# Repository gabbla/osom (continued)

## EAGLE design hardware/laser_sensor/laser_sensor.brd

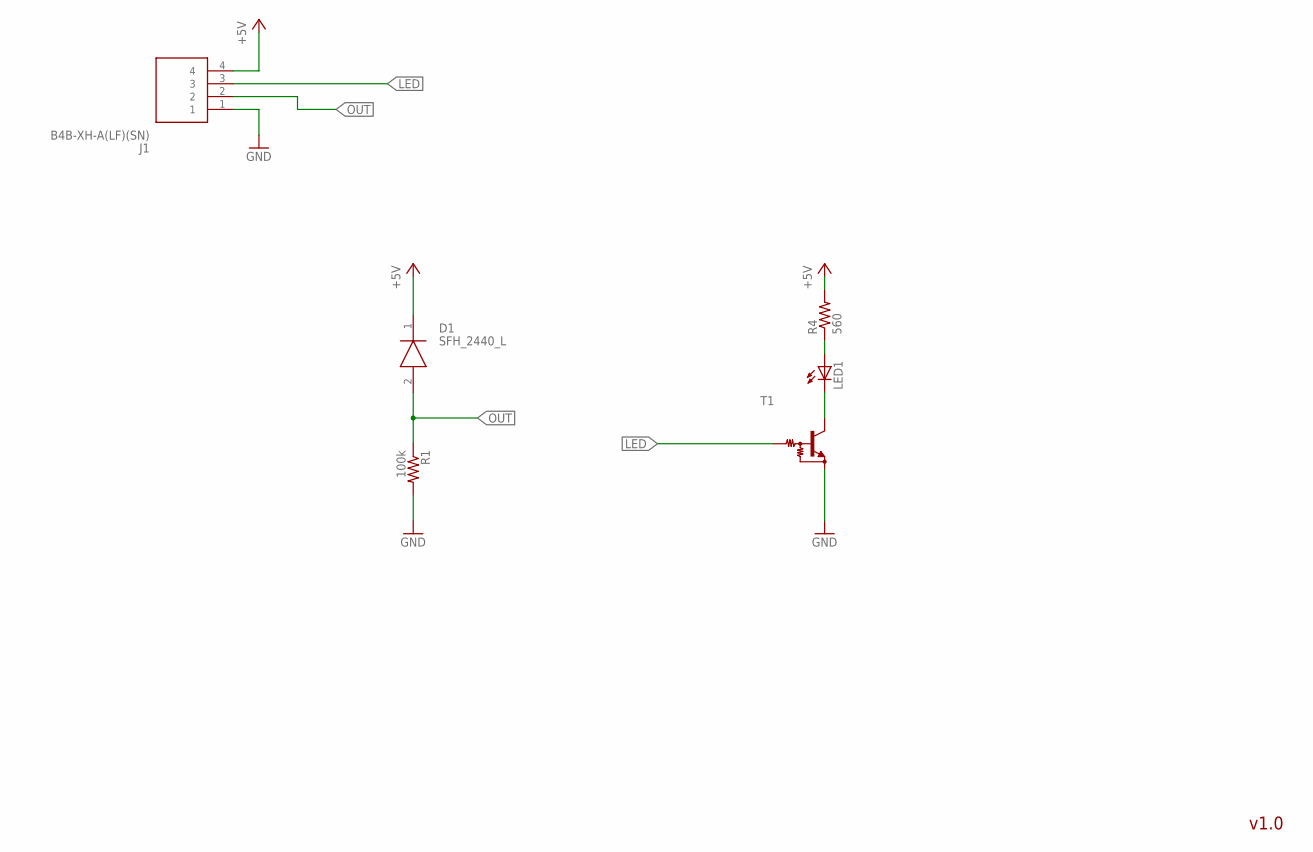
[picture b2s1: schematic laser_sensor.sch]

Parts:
D1: SFH_2440_L; SFH2440L
J1: B4B-XH-A(LF)(SN); SHDR4W64P0X250_1X4_1240X575X70
LED1: LED3MM
R1: 100k; R0603
R4: 560; R0603
T1: MUN2214T1-NPN_DRIVER-SC59-BEC; SC59-BEC

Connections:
+5V: D1.1 (ANODE), J1.4, R4.2
GND: J1.1, R1.2, T1.E
LED: J1.3, T1.B
unnamed: LED1.A, R4.1
unnamed: LED1.K (C), T1.C
OUT: D1.2 (CATHODE), J1.2, R1.1

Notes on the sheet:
v1.0

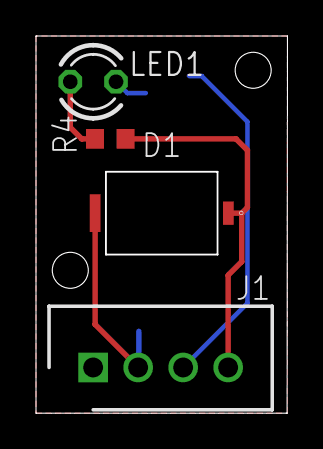
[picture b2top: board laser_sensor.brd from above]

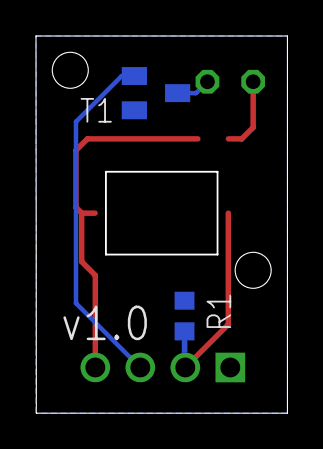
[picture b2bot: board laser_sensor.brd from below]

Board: 2 copper layers, 13.9 x 20.9 mm, 6 parts (2 on the bottom side), 6 nets.

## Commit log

2018-04-15 README.md edited online with Bitbucket
2018-07-07 First draft about CC2541
2018-07-07 First hardwere draft
2018-07-15 - Eagle libraries added - Initial import
2018-07-18 Pin functions and number updated
2018-07-18 IAR test workspace initial commit
2018-07-19 Added CC2541 links
2018-07-29 First IAR workspace draft THAT COMPILES and LINK A no-limit license is needed
2018-08-08 First draft about new arch
2018-08-09 Added debug uart Minor changes
2018-08-09 IAR test deletion
2018-08-09 Gitignore added
2018-08-09 IAR stuff.. to lazy to track them. I won't use them anymore
2018-08-09 PIC32 datasheet added
2018-08-09 Various Eagle library added
2018-08-10 Added regexp to exclude Eagle cad temp files
2018-08-10 Update hw analysis
2018-08-10 Tables fix
2018-08-10 Typo
2018-08-10 Ignore pdf
2018-08-10 .gitignore cleanup
2018-08-10 PIC32Mx110F016B and MC2200 library added
2018-08-10 .gitignore updated
2018-08-10 Readme updated with MCP product's page
2018-08-10 PIC added
2018-08-11 Library added
2018-08-12 Laser ctl pins are now on I/O Expander
2018-08-12 SYSOFF connected to the I/O Expander
2018-08-12 JST-XH libraries added
2018-08-12 TODOs added
2018-08-12 Added Bq24075
2018-08-12 Added some todos
2018-08-13 Vertical switch added
2018-08-13 Schema version 1.0alpha
2018-08-14 Ignoring also Eagle temp board files
2018-08-14 Some pins swapped to simplify the routing
2018-08-14 Most of the work is done. Fixing ground planes and power paths
2018-08-14 Ignoring board tmp files
2018-08-14 Routing is done. Waiting a check from a Sandro
2018-08-14 IAR folder removed from this repo
2018-08-14 TODOs updated
2018-08-14 Sync with .gitignore
2018-08-14 Laser sensor project created
2018-08-15 Photodiode library added
2018-08-15 First complete route for laser sensor
2018-08-15 Laser sensor gerber added
2018-08-16 Board images added
2018-08-16 laser sensor gerber updated
2018-08-16 CAM process to generate gerber for sensor added
2018-08-16 Updated sensor gerber
2018-08-16 Added main board gerber files
2018-08-16 Added cam file to generate main board gerber
2018-08-19 TPS6300x inductors changed
2018-08-19 Main board gerber updated
2018-08-19 Main board BOM added
2018-08-19 Added some libraries
2018-08-19 ignoring datasheets folder
2018-08-19 Laser sensor BOM added
2018-08-19 Main board schematic pdf added
2018-08-20 Fixed some stuff with Sandro's help. Main board gerber updated
2018-08-20 Schematics pdf prints added
2018-08-20 Version added
2018-08-21 Sorting files
2018-08-21 Assambly instruction
2018-08-21 README updated
2018-08-25 Added LICENSE
2018-08-25 Updated LICENCE
2018-08-25 Some confusion, added LICENCE
2018-09-04 Added revision info. PDF updated
2018-09-04 Image updated with produced PCB gerbers
2018-11-02 Added laser support model
2018-11-02 Added gitignore
2018-11-02 Added sensor support 3D model
2018-11-02 README.md updated
2018-11-02 Images added
2018-11-02 BOM added
2018-11-02 Hardware sync
2018-11-02 Analysis note added
2018-11-15 Fixed diode (#8) and battery polarity (#5)
2018-11-15 Removed I/O expander
2018-11-15 Removed selectable voltage on laser connectors
2018-11-15 Removed MCP2200
2018-11-15 Readme updated, still wip
2018-11-15 Added BQ27441 library
2018-11-15 BQ27441 symbol fix
2018-11-15 Added BQ27441, still wip
2018-11-16 minor grammar fix
2018-11-16 Communication addede
2018-11-16 Added PIC32MX274F256D lib
2018-11-16 Added HM11 library
2018-11-16 Switched HM10 with a more compact HM11
2018-11-19 New symbol for usb connector
2018-11-19 PIC32MX274 symbol edited
2018-11-19 PIC32MX274F256 added
2018-11-20 The whole exposed pad is now connected
2018-11-20 Symbol pin moved
2018-11-20 PIC pin assigned, LiPo gauge connected
2018-11-20 Some stuff added
2018-11-21 Minor stuff
2018-11-26 SN74AHC1G08DBVR added
2018-11-26 SN74AHC1G08DBVR symbol fix
2018-11-26 Laser ctl logic added
2018-11-30 mirror support added
2018-12-18 laser resize 12 -> 6 mm
2019-01-02 notes added
2019-01-02 fixed led off while charging the board in off state
2019-01-02 new board dimension
2019-01-02 part renumbered
2019-01-02 pcb: power routed
2019-01-05 wip, mostly done
2019-01-05 removed garbage
2019-01-18 sync meta
2019-01-18 new board 4layer
2019-01-18 new outline size
2019-01-18 new size 68x55
2019-01-18 power added
2019-01-19 usb: centered
2019-01-19 antenna draft
2019-01-19 exposed pad fix
2019-01-19 switch centered
2019-01-20 label fix
2019-01-23 first layout draft
2019-01-23 minor fix on libs
2019-01-23 sensor redesign
2019-01-23 SFH2440 symbol added
2019-01-24 dimension fix according to the manufacturer
2019-02-08 added 74LVC1G32SE
2019-02-08 aligned with GF suggestion, waiting approval
2019-02-08 metadata sync
2019-02-12 prefix added
2019-02-12 part renumber
2019-02-12 cam job for jlcpcb added (4 layers)
2019-02-12 cleanup
2019-02-12 cam job update
2019-02-12 gerber added
2019-02-12 cam job 2 layers added
2019-02-12 gerber update with labels
2019-02-12 updated pdf added
2019-02-12 updated pdf added for sensor
2019-02-13 bom added (generated from eagle)
2019-02-21 changed some transistors
2019-02-21 changed 887 package to 0805
2019-04-21 .gitignore update
2019-09-13 readme: name changed
